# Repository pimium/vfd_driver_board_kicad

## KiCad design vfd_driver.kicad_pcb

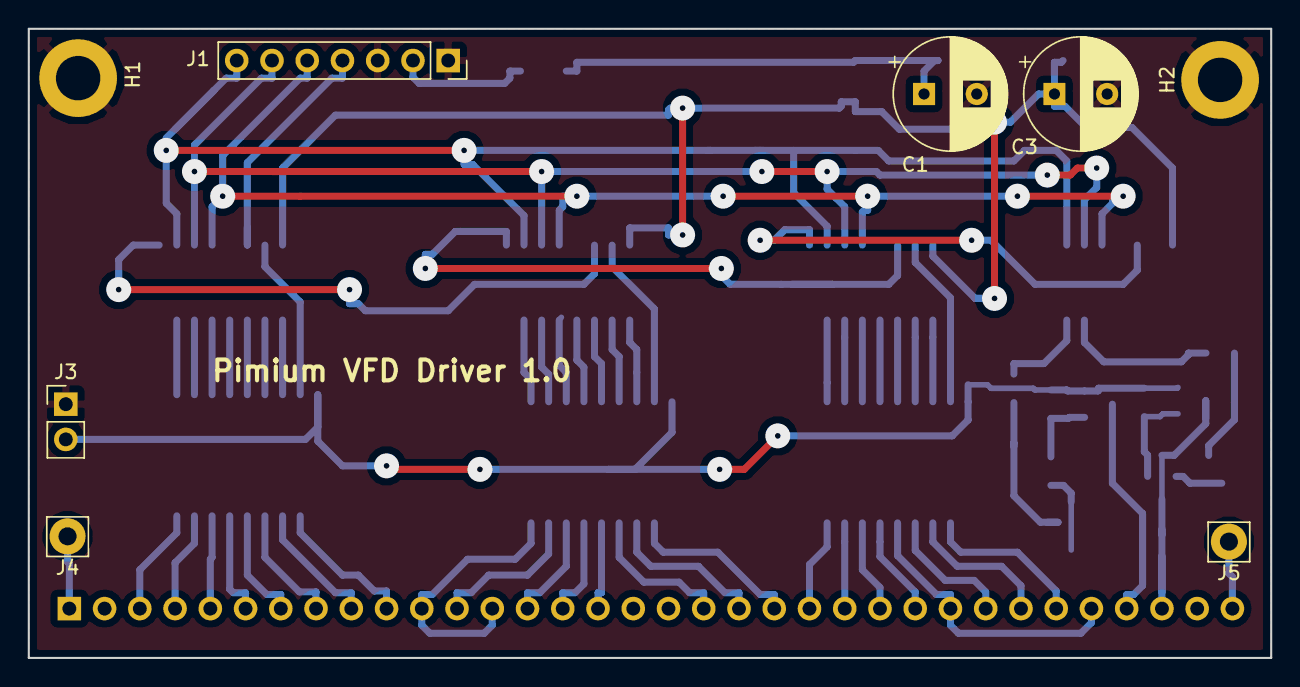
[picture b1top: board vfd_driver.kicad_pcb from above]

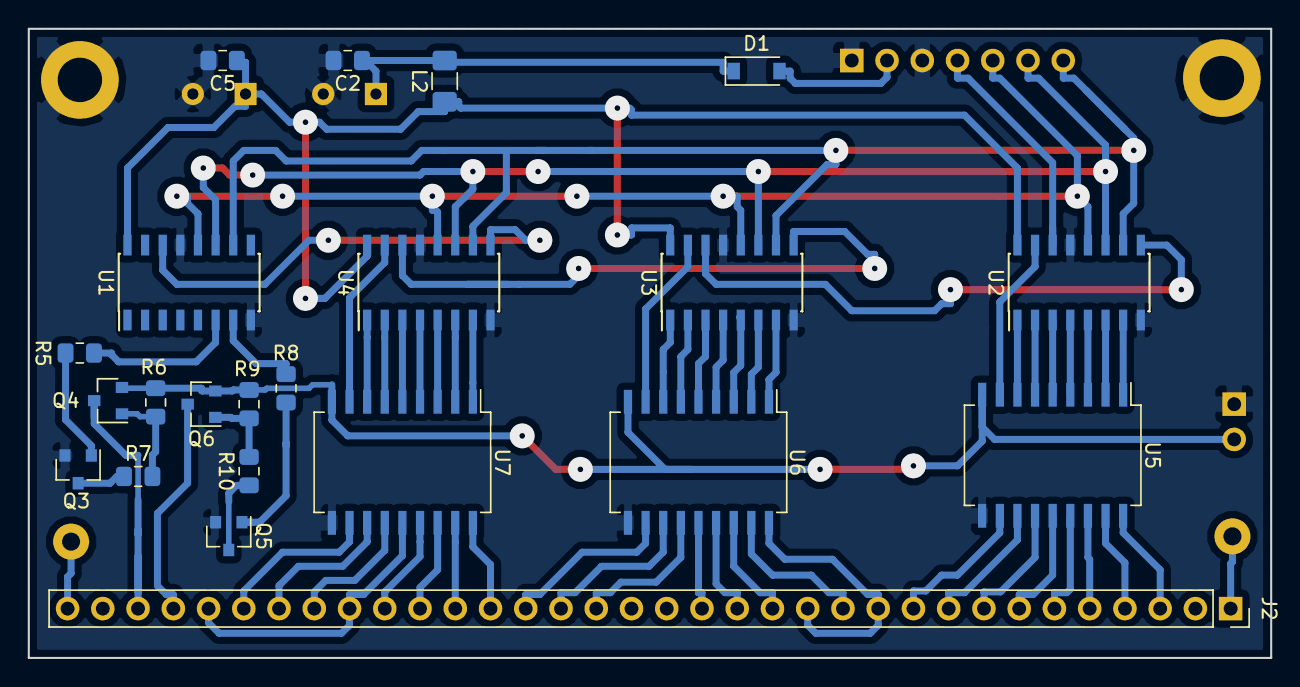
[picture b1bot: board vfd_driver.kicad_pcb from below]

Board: 2 copper layers, 89.5 x 45.3 mm, 30 parts (22 on the bottom side), 72 nets.

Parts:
C1, C3: 10u; CP_Radial_D8.0mm_P3.80mm
C2: 100n; C_0805_2012Metric_Pad1.15x1.40mm_HandSolder
C5: 10n; C_0805_2012Metric_Pad1.15x1.40mm_HandSolder
D1: SD103BW; D_SOD-123
H1, H2: MH; MountingHole_3.2mm_M3_DIN965_Pad
J1: Input; PinSocket_1x07_P2.54mm_Vertical
J2: futaba_7_lt_44z; PinSocket_1x34_P2.54mm_Vertical
J3: High Volt; PinHeader_1x02_P2.54mm_Vertical
J4: FIL_n; Pin_D1.4mm_L8.5mm_W2.8mm_FlatFork
J5: FIL_p; Pin_D1.4mm_L8.5mm_W2.8mm_FlatFork
L2: 33; L_1206_3216Metric_Pad1.42x1.75mm_HandSolder
Q3, Q5: BC817; SOT-23
Q4, Q6: BC807; SOT-23
R5, R7, R8, R10: 33k; R_0805_2012Metric_Pad1.15x1.40mm_HandSolder
R6, R9: 100k; R_0805_2012Metric_Pad1.15x1.40mm_HandSolder
U1, U2, U3, U4: 74HC595; SOIC-16_3.9x9.9mm_P1.27mm
U5, U6, U7: TBD62783A; SOP-18_7.0x12.5mm_P1.27mm

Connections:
+36V: J3.2, Q4.2, Q6.2, R6.1, R9.1, U5.9, U6.9, U7.9
/DATA: J1.4, U2.14
/G1: J2.26, J2.30, U7.14
/G2: J2.23, U7.17
/G3: J2.20, U6.12
/G4: J2.16, U6.14
/G5: J2.11, J2.13, U6.18
/G6: J2.8, U5.13
/G7: J2.5, U5.16
/Q0: U2.9, U3.14
/Q1: U3.9, U4.14
/Q1A: U2.15, U5.8
/Q1B: U2.1, U5.7
/Q1C: U2.2, U5.6
/Q1D: U2.3, U5.5
/Q1E: U2.4, U5.4
/Q1F: U2.5, U5.3
/Q1G: U2.6, U5.2
/Q1H: U2.7, U5.1
/Q2: U1.14, U4.9
/Q2A: U3.15, U6.8
/Q2B: U3.1, U6.7
/Q2C: U3.2, U6.6
/Q2D: U3.3, U6.5
/Q2E: U3.4, U6.4
/Q2F: U3.5, U6.3
/Q2G: U3.6, U6.2
/Q2H: U3.7, U6.1
/Q3A: U4.15, U7.8
/Q3B: U4.1, U7.7
/Q3C: U4.2, U7.6
/Q3D: U4.3, U7.5
/Q3E: U4.4, U7.4
/Q3F: U4.5, U7.3
/Q3G: U4.6, U7.2
/Q3H: U4.7, U7.1
/Q4G: R5.1, U1.6
/Q4H: R8.1, U1.7
/RCLK: J1.5, U1.12, U2.12, U3.12, U4.12
/S1: J2.15, U6.15
/S2: J2.14, U6.16
/S3: J2.12, U6.17
/S4: J2.10, U5.11
/S5: J2.9, U5.12
/S6: J2.7, U5.14
/S7: J2.6, U5.15
/S8: J2.4, U5.17
/S9: J2.3, U5.18
/S10: J2.32, Q4.3
/S11: J2.31, Q6.3
/S12: J2.29, U7.11
/SRCLK: J1.6, U1.11, U2.11, U3.11, U4.11
/a: J2.28, U7.12
/b: J2.27, U7.13
/c: J2.25, U7.15
/d: J2.24, U7.16
/e: J2.22, U7.18
/f: J2.21, U6.11
/g: J2.19, U6.13
/~SRCLR: J1.7, U1.10, U2.10, U3.10, U4.10
GND: C1.2, C2.2, C3.2, C5.2, H1.1, H2.1, J1.1, J1.3, J3.1, Q3.2, Q5.2, U1.8, U1.13, U2.8, U2.13, U3.8, U3.13, U4.8, U4.13, U5.10, U6.10, U7.10
unnamed: C1.1, C2.1, D1.1, L2.2
unnamed: J2.1, J4.1
unnamed: J2.34, J5.1
unnamed: Q3.1, R5.2
unnamed: Q3.3, R7.1
unnamed: Q4.1, R6.2, R7.2
unnamed: Q5.1, R8.2
unnamed: Q5.3, R10.1
unnamed: Q6.1, R9.2, R10.2
VCC: C3.1, C5.1, L2.1, U1.16, U2.16, U3.16, U4.16
VDD: D1.2, J1.2

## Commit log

2019-04-25 remove resistor and align comments
2019-04-26 start arranging label
2019-04-27 add a protecting diode to the power input. make sure the right thing are pushed.
2019-04-27 remove unconnected wires
2019-04-27 arranging labels
